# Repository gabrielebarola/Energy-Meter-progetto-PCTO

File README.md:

<div id="top"></div>
<!-- PROJECT LOGO -->
<br />
<div align="center">

<h3 align="center">Energy meter</h3>

  <p align="center">
    Progetto per il percorso di PCTO 2021/2022
  </p>
</div>

<!-- ABOUT THE PROJECT -->
## Il progetto

Cercando di collegare l'attività del PCTO con le tematiche trattate in educazione civica durante l'anno, ho deciso di sviluppare un sistema in grado di monitorare i parametri necessari per mostrare all'utente in modo semplice lo stato dell'impianto elettrico della propria abitazione e lo storico dei consumi, con l'obiettivo di incentivare un utilizzo più consapevole dell'energia elettrica.

Il progetto unisce in unico pacchetto tutte le funzionalità di seguito riportate e analizzate nello specifico successivamente.

* MISURA DELLE PRINCIPALI GRANDEZZE DI UN IMPIANTO ELETTRICO
* CALCOLO DELLA POTENZA E DEL FATTORE DI POTENZA
* VISUALIZZAZIONE DEI DATI IN TEMPO REALE
* GRAFICI INTERATTIVI

## Altre tecnologie e software utilizzati

* [MicroPython](https://micropython.org/)
* [Kicad](https://www.kicad.org/)
* [VSCode](https://code.visualstudio.com/)
* [MicroWebSrv2](https://github.com/jczic/MicroWebSrv2)
* [Charts.js](https://github.com/chartjs/Chart.js)

## Screenshot

<div align="center">
  
</div>

## Presentazione per l'esame di stato

<div>
  
</div>

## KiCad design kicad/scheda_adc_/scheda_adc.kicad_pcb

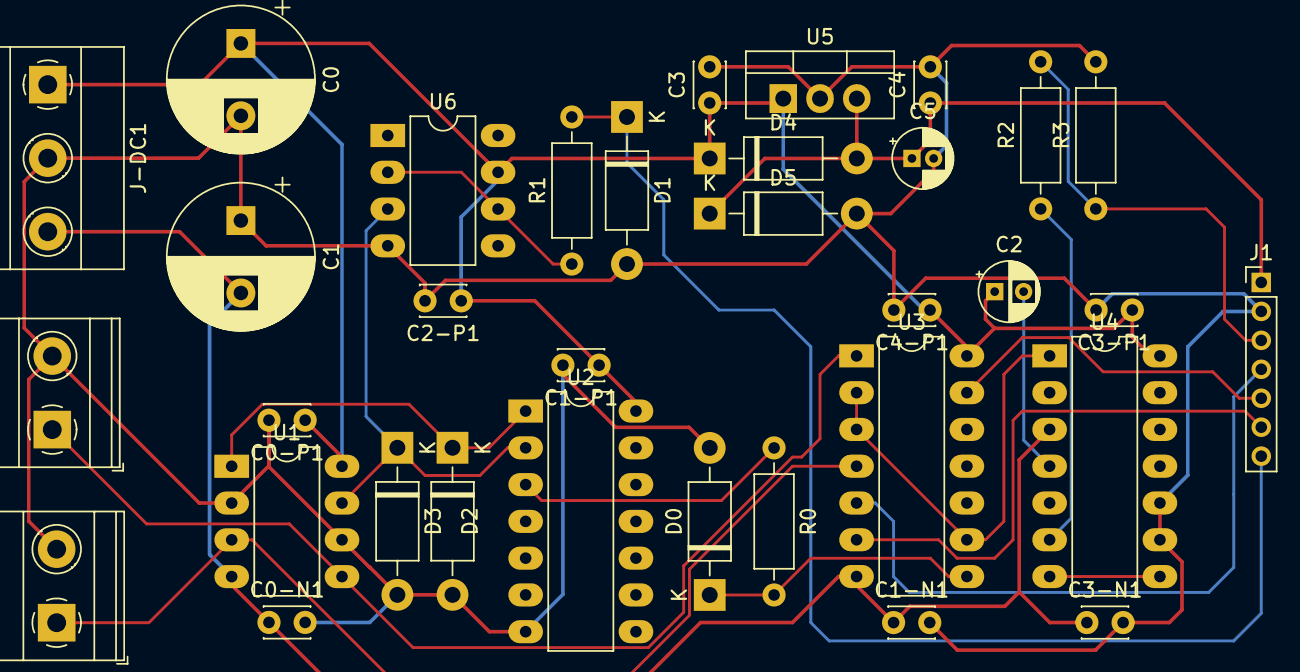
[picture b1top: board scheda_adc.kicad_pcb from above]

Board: 2 copper layers, 34 parts (0 on the bottom side), 20 nets.

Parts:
C0, C1: 330uF; CP_Radial_D10.0mm_P5.00mm
C0-N1, C0-P1, C1-N1, C1-P1, C2-P1, C3-N1, C3-P1, C4, C4-P1: 100nF; C_Disc_D3.0mm_W2.0mm_P2.50mm
C2: 4,7uF; CP_Radial_D4.0mm_P2.00mm
C3: 330nF; C_Disc_D3.0mm_W2.0mm_P2.50mm
C5: 47uF; CP_Radial_D4.0mm_P1.50mm
D0: 5V; D_DO-41_SOD81_P10.16mm_Horizontal
D1: 3,3V; D_DO-41_SOD81_P10.16mm_Horizontal
D2, D3: 1N4007; D_DO-41_SOD81_P10.16mm_Horizontal
D4, D5: 1N4001; D_DO-41_SOD81_P10.16mm_Horizontal
J1: Conn_01x07_Male; PinHeader_1x07_P2.00mm_Vertical
J-DC1: j; TerminalBlock_Phoenix_MKDS-1,5-3-5.08_1x03_P5.08mm_Horizont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
J-I1: Screw_Terminal_01x02; TerminalBlock_Phoenix_MKDS-1,5-2-5.08_1x02_P5.08mm_Horizont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
J-V1: Screw_Terminal_01x02; TerminalBlock_Phoenix_MKDS-1,5-2-5.08_1x02_P5.08mm_Horizont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
R0, R1: 1.5K; R_Axial_DIN0207_L6.3mm_D2.5mm_P10.16mm_Horizontal
R2, R3: 15k; R_Axial_DIN0207_L6.3mm_D2.5mm_P10.16mm_Horizontal
U1: LM358; DIP-8_W7.62mm_LongPads
U2: 4070; DIP-14_W7.62mm_LongPads
U3: 4066; DIP-14_W7.62mm_LongPads
U4: AD536A; DIP-14_W7.62mm_LongPads
U5: L7805; TO-220-3_Vertical
U6: CA3140; DIP-8_W7.62mm_LongPads

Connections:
+5V: C4.1, C5.1, D4.2 (A), D5.1 (K), J1.1, U5.3 (OUT)
+12V: C0.1, C0-P1.1, C1-P1.1, C2.1, C2-P1.1, C3.1, C3-P1.1, C4-P1.1, D4.1 (K), J-DC1.1, U1.8 (V+), U2.14 (VDD), U3.14 (VDD), U4.14 (Vs+), U5.1 (IN), U6.7 (V+)
-12V: C0-N1.1, C1.2, C1-N1.1, C3-N1.1, J-DC1.3, U1.4 (V-), U3.7 (VSS), U4.3 (Vs-)
ADC_IN: J1.3, R2.2, R3.1
EN_I: J1.4, U3.5
EN_P: J1.6, U3.6
EN_V: J1.5, U3.13
FREQUENCY: D1.1 (K), J1.7, R1.2
GNDA: C0.2, C0-N1.2, C0-P1.2, C1.1, C1-N1.2, C1-P1.2, C2-P1.2, C3.2, C3-N1.2, C3-P1.2, C4.2, C4-P1.2, C5.2, D0.2 (A), D1.2 (A), D2.2 (A), D3.2 (A), D5.2 (A), J1.2, J-DC1.2, J-I1.2, J-V1.2, R3.2, U1.2 (-), U1.6 (-), U2.7 (VSS), U4.9 (Rl), U4.10 (COM), U5.2 (GND), U6.4 (V-)
unnamed: C2.2, U4.4 (Cav)
unnamed: D2.1 (K), U1.1, U2.1
unnamed: D3.1 (K), U1.7, U2.2, U6.3 (+)
unnamed: R0.1, U2.3
unnamed: R1.1, U6.2 (-), U6.6
unnamed: U3.2, U3.3, U3.9, U4.1 (Vin)
unnamed: R2.1, U4.6 (Vout)
unnamed: U4.7 (Buf_in), U4.8 (Iout)
PHASE: D0.1 (K), R0.2, U3.8
V_CORRENTE: J-I1.1, U1.3 (+), U3.4
V_TENSIONE: J-V1.1, U1.5 (+), U3.1

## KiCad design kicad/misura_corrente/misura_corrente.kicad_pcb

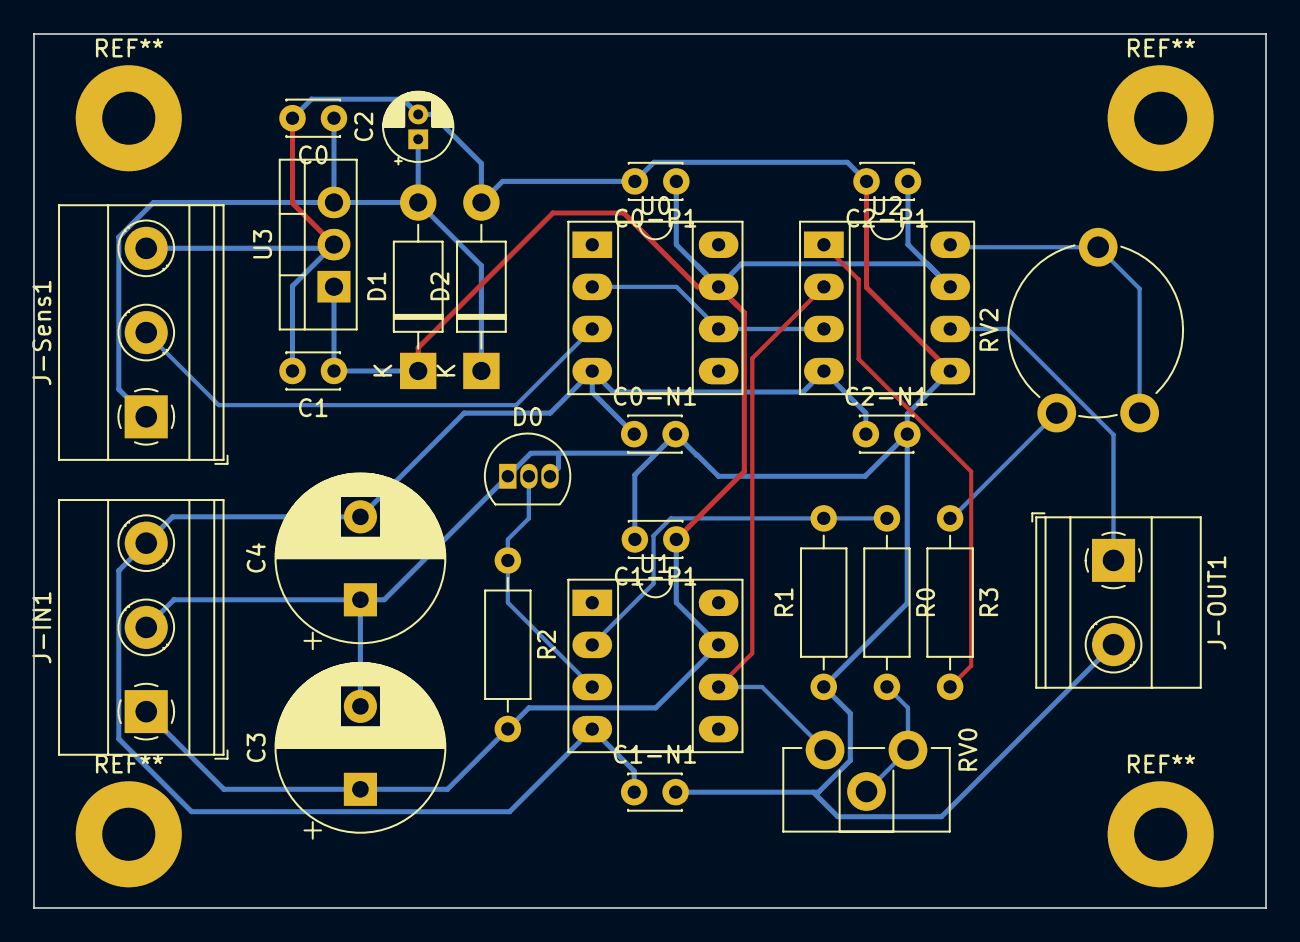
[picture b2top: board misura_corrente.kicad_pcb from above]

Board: 2 copper layers, 74.3 x 52.7 mm, 27 parts (0 on the bottom side), 14 nets.

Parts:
C0, C0-N1, C0-P1, C1-N1, C1-P1, C2-N1, C2-P1: 100nF; C_Disc_D3.0mm_W2.0mm_P2.50mm
C1: 330nF; C_Disc_D3.0mm_W2.0mm_P2.50mm
C2: 47uF; CP_Radial_D4.0mm_P1.50mm
C3, C4: 330uF; CP_Radial_D10.0mm_P5.00mm
D0: LM336z25; TO-92L_Inline
D1, D2: 1N4001; D_DO-41_SOD81_P10.16mm_Horizontal
J-IN1: j; TerminalBlock_Phoenix_MKDS-1,5-3-5.08_1x03_P5.08mm_Horizont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
J-OUT1: Screw_Terminal_01x02; TerminalBlock_Phoenix_MKDS-1,5-2-5.08_1x02_P5.08mm_Horizont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
J-Sens1: CSLA2CD; TerminalBlock_Phoenix_MKDS-1,5-3-5.08_1x03_P5.08mm_Horizont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
R0: 5.6k; R_Axial_DIN0207_L6.3mm_D2.5mm_P10.16mm_Horizontal
R1: 10k; R_Axial_DIN0207_L6.3mm_D2.5mm_P10.16mm_Horizontal
R2: 3.6k; R_Axial_DIN0207_L6.3mm_D2.5mm_P10.16mm_Horizontal
R3: 8.2k; R_Axial_DIN0207_L6.3mm_D2.5mm_P10.16mm_Horizontal
RV0: 2.2k; Potentiometer_ACP_CA9-H2,5_Horizontal
RV2: 2.2k; Potentiometer_Piher_PT-10-V10_Vertical
U0, U1: CA3140; DIP-8_W7.62mm_Socket_LongPads
U2: INA111; DIP-8_W7.62mm_Socket_LongPads
U3: L7808; TO-220-3_Vertical

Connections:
+8V: C0.1, C2.1, D1.2 (A), D2.1 (K), J-Sens1.1, U3.3 (OUT)
+12V: C0-P1.1, C1.1, C1-P1.1, C2-P1.1, C3.1, D1.1 (K), J-IN1.1, R2.2, U0.7 (V+), U1.7 (V+), U2.7 (V+), U3.1 (IN)
-12V: C0-N1.1, C1-N1.1, C2-N1.1, C4.2, J-IN1.3, U0.4 (V-), U1.4 (V-), U2.4 (V-)
GNDA: C0.2, C0-N1.2, C0-P1.2, C1.2, C1-N1.2, C1-P1.2, C2.2, C2-N1.2, C2-P1.2, C3.2, C4.1, D0.1 (Adj), D0.3 (V-), D2.2 (A), J-IN1.2, J-OUT1.2, J-Sens1.3, R1.1, U2.5 (Ref), U3.2 (GND)
I-SENS: U0.2 (-), U0.6, U2.3 (+)
I-SIN-OUT: J-OUT1.1, U2.6
unnamed: D0.2 (V+), R2.1, U1.3 (+)
unnamed: J-Sens1.2, U0.3 (+)
unnamed: R0.1, R1.2, U1.2 (-)
unnamed: R0.2, RV0.1, RV0.2
unnamed: R3.1, RV2.3
unnamed: R3.2, U2.1 (Rg)
unnamed: RV2.1, RV2.2, U2.8 (Rg)
VREF: RV0.3, U1.6, U2.2 (-)

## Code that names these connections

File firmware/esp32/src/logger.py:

from machine import Pin, ADC, time_pulse_us
from micropython import const
import time


_ref = const(2450000)
_ref_v = const(250)
_ref_i = const(25)

_offset = const(142000)  # misurato su ingresso adc collegato a massa 142000


class Logger:
    def __init__(self, freq, adc, en_i, en_v, en_p):

        self.freq = Pin(freq, Pin.IN)
        self.adc = ADC(Pin(adc, Pin.IN), atten=ADC.ATTN_11DB)

        self.en_i = Pin(en_i, Pin.OUT)
        self.en_v = Pin(en_v, Pin.OUT)
        self.en_p = Pin(en_p, Pin.OUT)

        self.readings = [0.0, 0.0, 0.0, 0.0]
        self._reset_en()

    def _reset_en(self):
        self.en_i.off()
        self.en_v.off()
        self.en_p.off()

    def read_freq(self):
        _, half = time_pulse_us(self.freq, 1), time_pulse_us(self.freq, 1)
        period = 2 * half
        freq = 1e6 / (period)
        return round(freq, 1)

    def _read_samples(self, samples):
        l = []
        time.sleep_ms(600)  # da datasheet ad536

        for i in range(samples):

            time.sleep_us(15)
            val = self.adc.read_uv()
            l.append(val)

        return (sum(l) / len(l)) - _offset

    def read_v(self, samples=50):
        self._reset_en()
        self.en_v.on()
        mean = self._read_samples(samples)

        return (mean / _ref) * _ref_v

    def read_i(self, samples=50):
        self._reset_en()
        self.en_i.on()
        mean = self._read_samples(samples)

        return (mean / _ref) * _ref_i

    def read_p(self, samples=50):
        self._reset_en()
        self.en_p.on()
        mean = self._read_samples(samples)  # valore efficace

        dc = (mean / _ref) ** 2  # duty cycle

        phase = dc * 180

        return int(phase)

    def read(self):
        self.readings[0] = self.read_v()
        self.readings[1] = self.read_i()
        self.readings[2] = self.read_freq()
        self.readings[3] = self.read_p()

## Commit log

2022-03-08 schema elettrico fino a ina111
2022-03-21 aggiunte footprint
2022-03-22 fatto pcb per millefori
2022-03-22 stampa pdf
2022-04-05 configurazione vscode e documento
2022-04-05 iniziata doc con latex
2022-04-11 added todo
2022-04-12 corrente iniziata
2022-04-12 iniziato firmware
2022-04-13 creata pagina di prova
2022-04-13 prototipo pagina web
2022-04-20 fine pagina di prova
2022-04-25 iniziato grafico 24h
2022-05-16 iniziata schda acquisizione
2022-05-16 schema elettrico misura fase
2022-05-16 inizio modifica socket e passaggio a request
2022-06-01 continuazione documentazione corrente (todo 3d)
2022-06-01 main
2022-06-20 fine progetto principale
2022-06-20 screenshot
2022-06-20 readme
